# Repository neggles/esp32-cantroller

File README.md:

# EltekController

This is a little board I whipped up to connect to my [Eltek Flatpack2 Breakout Board](https://github.com/neg2led/EltekFlatpack2) but it should be useful as a general CANBUS control board with wide voltage input.

Most of the parts on the board are outfitted with their LCSC code for KiKit's JLCPCB SMT fab autogeneration. 

I'm using an ESP32-S2-WROOM / ESP32-S2-WROVER module, abusing the on-board USB DFU to avoid having a USB-UART IC.

There's a header designed to take a cheap AliExpress 1.3" 128x64 OLED module, a Qwiic connector for... reasons? and a footprint that matches ESP-Prog pinout and works with:

- Any 2x3 1.27mm IDC header, shrouded or unshrouded, or appropriate pogopin matrix
- Tag-Connect TC2030-NL programming pogopin connector
- Harwin Gecko 1.25mm pitch wire-to-board connector

There's probably some other stuff that'll fit just fine as well.

The DC-DC converter module is a fancy TDK-Lambda one which I got a whole bunch of from Digikey's Chip Outpost for like 20c each, when I run out I'll probably make another version using either an on-board converter or another module, one that outputs 5V so the Qwiic connector is actually in-spec and the XC6220 isn't solely used for USB-bus-powered mode.

To be honest, expect to see the on-board DC-DC version soon, because this module is C H O N K Y.

I've probably made some really bad design choices here, please don't judge me.

## Repository Structure
- `EltekController` contains the main schematics and board drawing
- `EltekController/EltekController.pretty` contains the board-specific footprints
- `EltekController/shapes3D` contains the 3D models for parts on the board (and a bunch of extras from my various experiments)

## Building
Simply call `make` in the top-top level directory. The `build` directory will then contain:

- the main board
- A panelized version of said board
- zipped gerbers for the boards you can directly use for manufacturing
- zipped gerbers and SMT assembly BOM/position files for JLCPCB's SMT assembly service for the single-board version.

Makefile uses [Jan Mrázek](https://github.com/yaqwsx)'s [KiKit](https://github.com/yaqwsx/KiKit), which I cannot recommend enough, and therefore has to be available on your system.

Jan's [jlcparts](https://yaqwsx.github.io/jlcparts/) app was also extremely useful in narrowing down part choices based on what JLCPCB have available.

-----
### **IMPORTANT NOTE:** If you give JLCPCB these files as-is, *please* verify the orientation of every part before submitting.

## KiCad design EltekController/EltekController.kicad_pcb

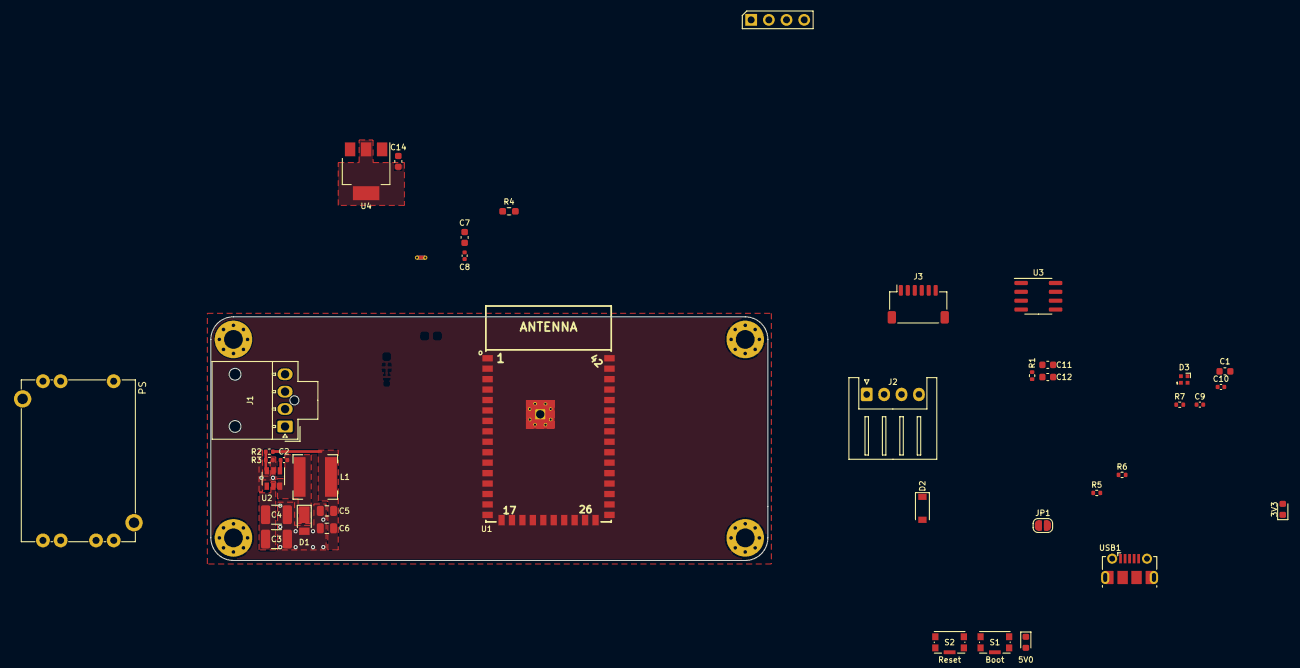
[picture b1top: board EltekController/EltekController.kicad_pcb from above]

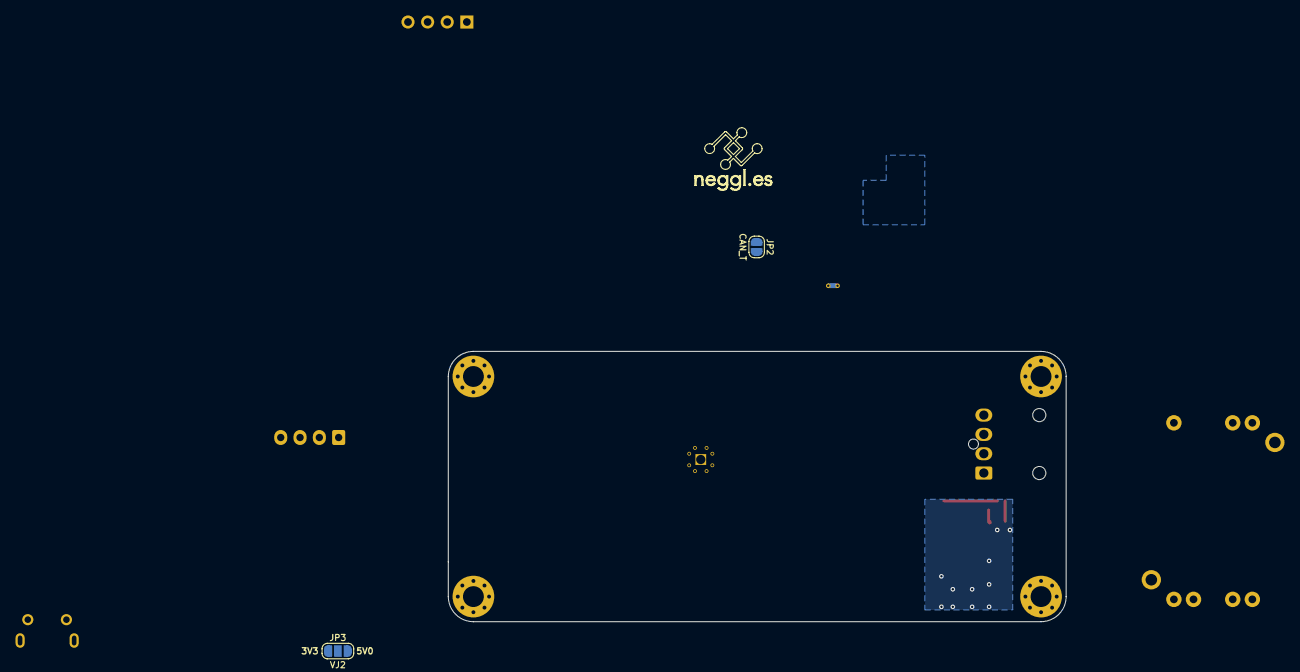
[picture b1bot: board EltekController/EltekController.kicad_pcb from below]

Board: 2 copper layers, 80.0 x 35.0 mm, 47 parts (3 on the bottom side), 31 nets.

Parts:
C1, C7: 10uF; C_0603_1608Metric
C2, C8, C9, C10: 100nF; C_0402_1005Metric
C3, C4: 2.2uF; C_1210_3225Metric_Pad1.33x2.70mm_HandSolder
C5, C6: 22uF; C_0805_2012Metric
C11, C14: 22uF; C_0603_1608Metric
C12: 100nF; C_0603_1608Metric
D1: SS210; D_PowerDI-123
D2: B5819W; D_SOD-123
D3: RGB; DY-S1515065_RGBC_6805-5T
D4: 3V3; LED_0603_1608Metric_SnapModel
D5: 5V0; LED_0603_1608Metric_SnapModel
H1, H2, H3, H4: MP; MountingHole_2.7mm_M2.5_Pad_Via
I2C1: OLED; OLED_SSD1315_128x64_1.3_I2C_New_Silhouette
J1: CANBUS; Molex_Nano-Fit_105309-xx04_1x04_P2.50mm_Vertical_Horizontal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
J2: Display; JST_XH_S4B-XH-A_1x04_P2.50mm_Horizontal
J3: ESP_PROG; JST_SH_SM06B-SRSS-TB_1x06-1MP_P1.00mm_Horizontal_3D
JP1: VPP_EN; SolderJumper-2_P1.3mm_Open_RoundedPad1.0x1.5mm
JP2: CAN_T; SolderJumper-2_P1.3mm_Open_RoundedPad1.0x1.5mm
JP3: VJ2; SolderJumper-3_P1.3mm_Open_RoundedPad1.0x1.5mm_NumberLabels
L1: 33uH; L_Sunlord_SWPA6028S
LOGO1: Logo_Open_Hardware_Small; neggle-logo-0.12
NT1: GND_TIE; NetTie-2_THT_Pad0.3mm
PS: Converter_DCDC_TDK-Lambda_CC3-xxxxxF-E
R1: 10K; R_0402_1005Metric
R2: 68K; R_0402_1005Metric
R3: 12K; R_0402_1005Metric
R4: 120R; R_0603_1608Metric_Pad0.98x0.95mm_HandSolder
R5: 22R; R_0402_1005Metric
R6, R7: 1K; R_0402_1005Metric
S1: Boot; SW_Push_1P1T-SH_NO_CK_KMR2xxG_3D
S2: Reset; SW_Push_1P1T-SH_NO_CK_KMR2xxG_3D
U1: ESP32-S2-WROVER; ESP32-S2-WROVER_and_WROOM(PCB,-I(IPEX))-Universal
U2: LMR16006XDDCR; SOT-23-6
U3: MAX3051ESA; SOIC-8_3.9x4.9mm_P1.27mm
U4: AMS1117-3.3; SOT-223-3_TabPin2
USB1: USB-OTG; USB_Micro-B_Molex-105017-0001

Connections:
+3V3: C7.2, C8.1, C11.2, C12.2, C14.2, D4.2, I2C1.2, JP1.1, JP3.3, R1.2, U1.2, U3.3, U4.2
+5V: C5.2, C6.2, D2.1, D3.2, D5.2, JP3.1, L1.2, R2.2, U4.3
+48V: C3.1, C4.1, J1.1, U2.5
/CAN+: J1.2, JP2.2, U3.7
/CAN-: J1.3, R4.1, U3.6
/CAN_RX: U1.16, U3.4
/CAN_TX: U1.15, U3.1
/CB: C2.2, U2.1
/D_RXSDA: J2.4, U1.32
/D_TXSCL: J2.3, U1.31
/FB: R2.1, R3.2, U2.3
/LED_DAT: R5.1, U1.30
/OLED_SCL: I2C1.3, U1.10
/OLED_SDA: I2C1.4, U1.9
/SW: C2.1, D1.1, L1.1, U2.6
/UART_RX: J3.3, U1.38
/UART_TX: J3.1, U1.37
/USB_D+: U1.23, USB1.3
/USB_D-: U1.22, USB1.2
/VBUS: D2.2, USB1.1
/VCC_PROG: J3.5, JP1.2
/~BOOT: C9.2, J3.2, S1.2, U1.3
/~CAN_EN: U1.14, U3.5
/~RST: C1.1, C10.2, J3.6, R1.1, S2.2, U1.41
GND: C1.2, C3.2, C4.2, C5.1, C6.1, C7.1, C8.2, C9.1, C10.1, C11.1, C12.1, C14.1, D1.2, D3.4, H2.1, H3.1, H4.1, I2C1.1, J2.1, J3.4, J3.MP, NT1.2, R3.1, R6.1, R7.1, S1.1, S2.1, U1.1, U1.26, U1.42, U1.43, U2.2, U3.2, U3.8, U4.1, USB1.5, USB1.6
GNDPWR: H1.1, J1.4, NT1.1
unnamed: D3.1, R5.2
unnamed: D4.1, R6.2
unnamed: D5.1, R7.2
unnamed: J2.2, JP3.2
unnamed: JP2.1, R4.2

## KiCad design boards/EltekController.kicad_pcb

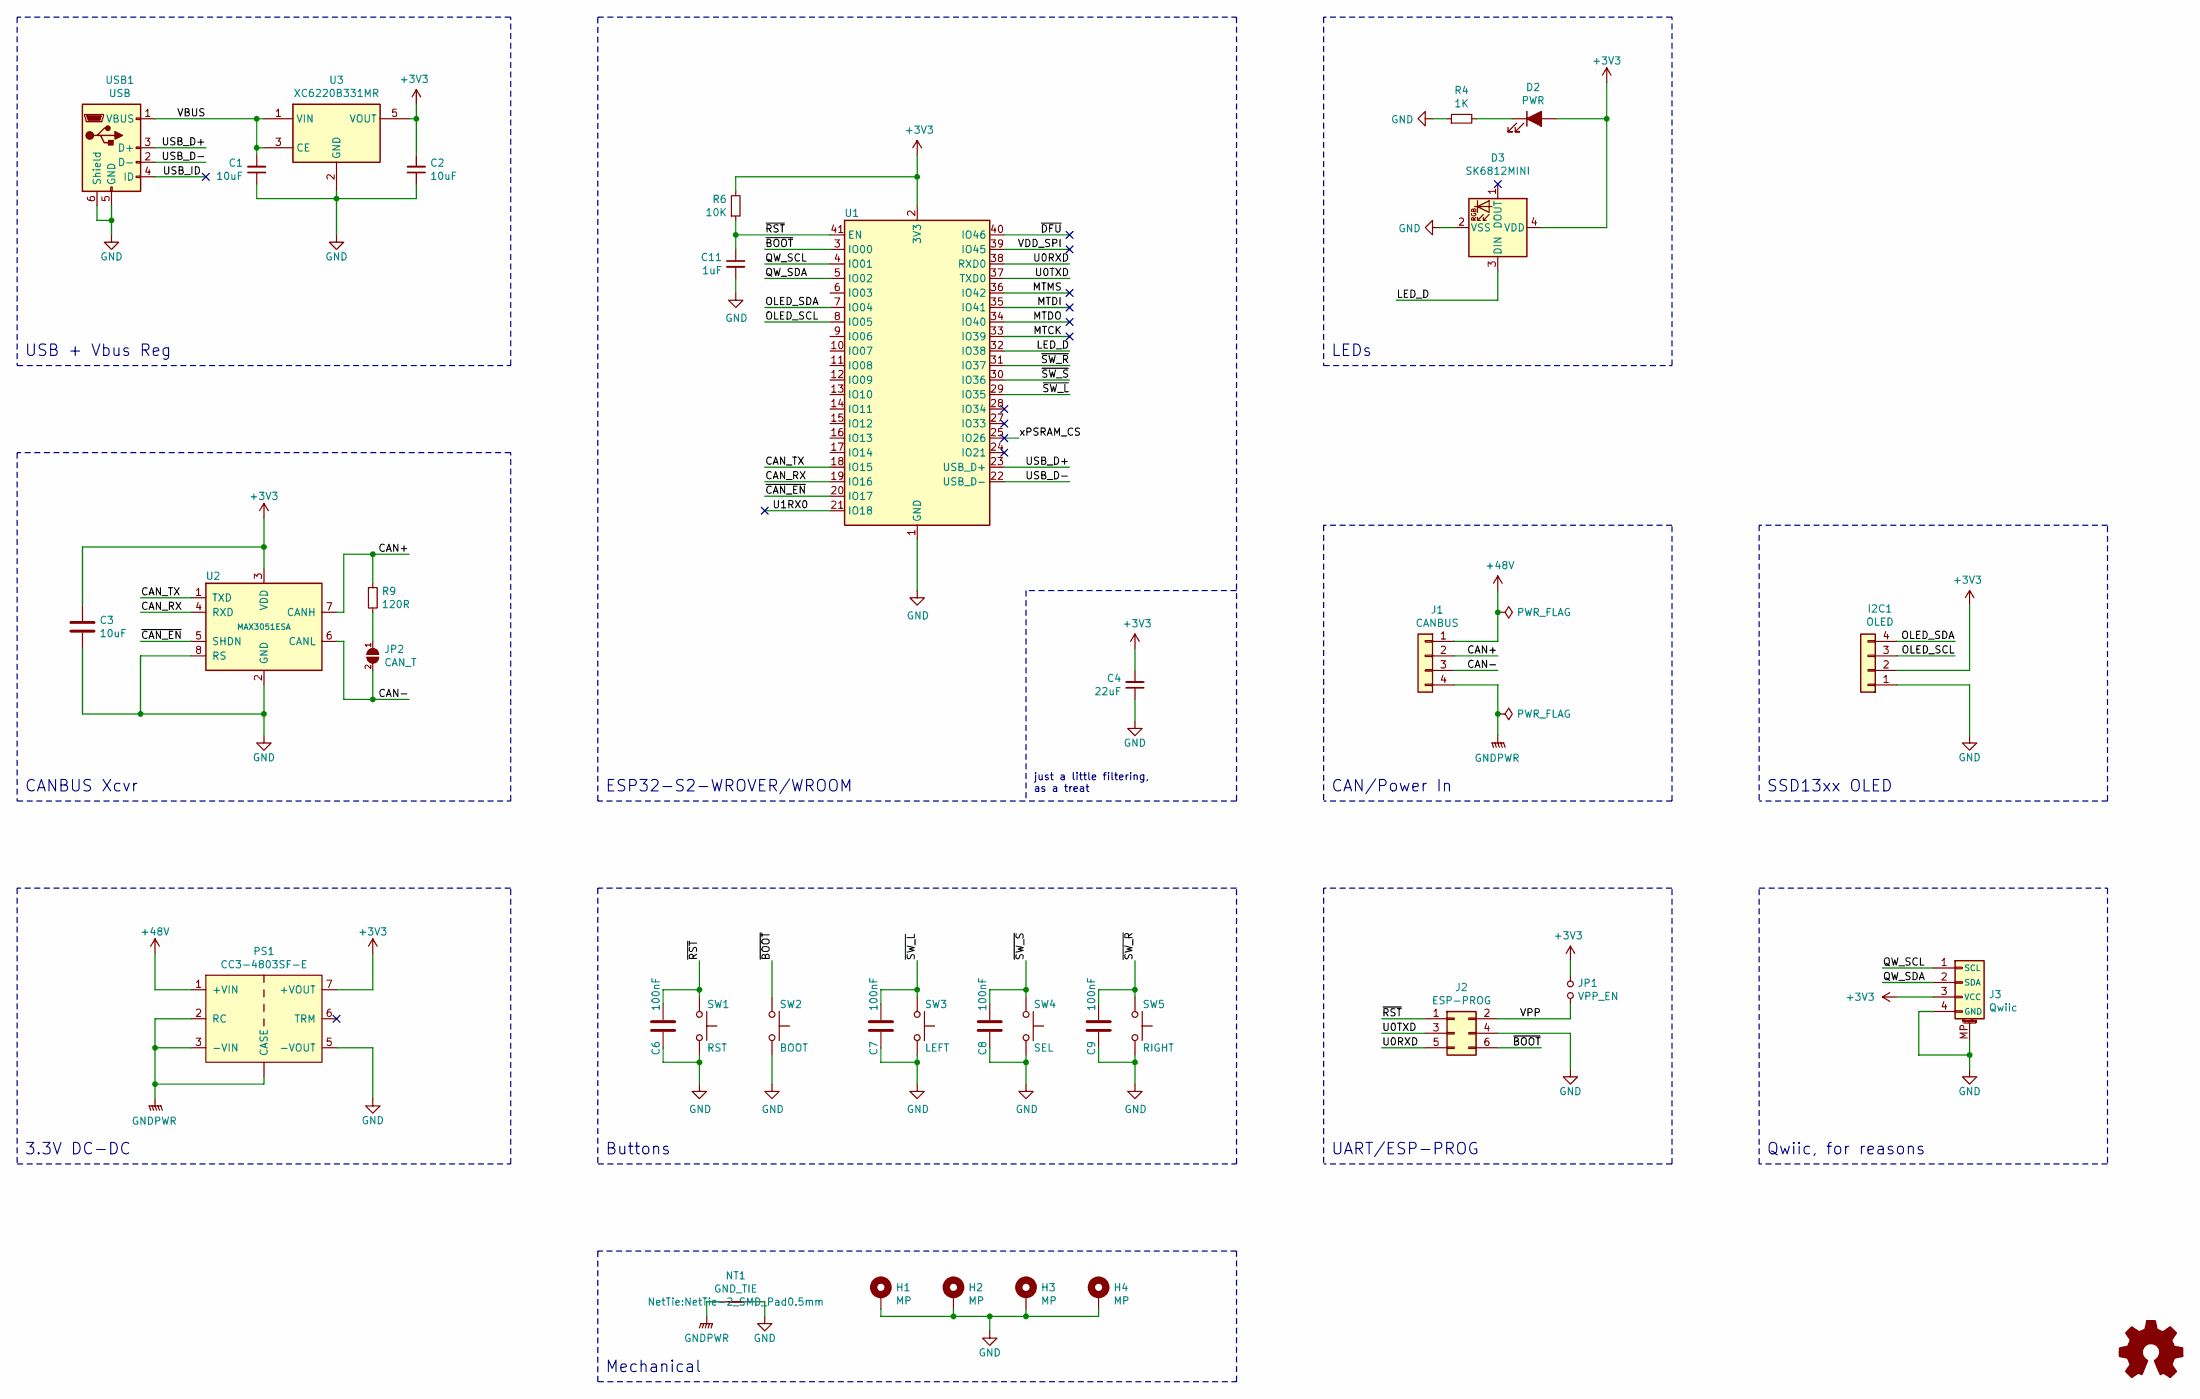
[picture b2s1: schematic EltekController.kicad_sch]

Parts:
C1, C2, C3: 10uF; C_0402_1005Metric; MPN CL05A106MQ5NUNC; LCSC C15525
C4: 22uF; C_0603_1608Metric; MPN CL10A226MQ8NRNC; LCSC C59461
C6, C7, C8, C9: 100nF; C_0402_1005Metric; MPN CL05B104KO5NNNC; LCSC C1525
C11: 1uF; C_0402_1005Metric; MPN CL05A105KA5NQNC; LCSC C52923
D2: PWR; LED_0603_1608Metric_SnapModel; MPN 19-217/GHC-YR1S2/3T; LCSC C72043
D3: SK6812MINI; LED_SK6812MINI_PLCC4_3.5x3.5mm_P1.75mm_3D
H1, H2, H3, H4: MP; MountingHole_2.7mm_M2.5_ISO7380_Pad_TopBottom
I2C1: OLED; OLED_SSD1315_128x64_1.3_I2C_New_Silhouette_Big3D
J1: CANBUS; Molex_Nano-Fit_105313-xx04_1x04_P2.50mm_Horizontal_3D
J2: ESP-PROG; Gecko-G125_PlusTC2030_IDCBox_2x03_P1.25mm_Vertical_3D
J3: Qwiic; JST_SH_SM04B-SRSS-TB_1x04-1MP_P1.00mm_Horizontal_3D
JP1: VPP_EN; SolderJumper-2_P1.3mm_Open_RoundedPad1.0x1.5mm
JP2: CAN_T; SolderJumper-2_P1.3mm_Open_RoundedPad1.0x1.5mm
LOGO1: Logo_Open_Hardware_Small; neggle-logo-0.12
NT1: GND_TIE; NetTie-2_SMD_Pad0.5mm
PS1: CC3-4803SF-E; Converter_DCDC_TDK-Lambda_CC3-xxxxxF-E
R4: 1K; R_0402_1005Metric; MPN 0402WGF1001TCE; LCSC C11702
R6: 10K; R_0402_1005Metric; MPN 0402WGF1002TCE; LCSC C25744
R9: 120R; R_0805_2012Metric_Pad1.15x1.40mm_HandSolder; MPN 0805W8F1200T5E; LCSC C17437
SW1: RST; KEY-SMD_4P-L4.2-W3.2-P2.20-LS5.1-TL; MPN K2-1808SN-A4SW-01; LCSC C92589
SW2: BOOT; KEY-SMD_4P-L4.2-W3.2-P2.20-LS5.1-TL; MPN K2-1808SN-A4SW-01; LCSC C92589
SW3: LEFT; KEY-SMD_4P-L4.2-W3.2-P2.20-LS5.1-TL; MPN K2-1808SN-A4SW-01; LCSC C92589
SW4: SEL; KEY-SMD_4P-L4.2-W3.2-P2.20-LS5.1-TL; MPN K2-1808SN-A4SW-01; LCSC C92589
SW5: RIGHT; KEY-SMD_4P-L4.2-W3.2-P2.20-LS5.1-TL; MPN K2-1808SN-A4SW-01; LCSC C92589
U1: ESP32-S2-WROVER; ESP32-S2-WROVER_and_WROOM(PCB,-I(IPEX))-Universal; MPN ESP32-S2-WROVER(4MB); LCSC C701333
U2: MAX3051ESA; SOIC-8_3.9x4.9mm_P1.27mm; MPN MAX3051ESA+T; LCSC C15648
U3: XC6220B331MR; SOT-23-5; LCSC C86534
USB1: USB; MICRO-USB-SMD_U254-051T-4BH83-F1S_C397452; LCSC C397452

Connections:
Board_1-+3V3: C2.2, C3.2, C4.2, D2.2 (A), D3.4 (VDD), I2C1.2, J3.3 (VCC), JP1.1, PS1.7 (+VOUT), R6.2, U1.2 (3V3), U2.3 (VDD), U3.5 (VOUT)
Board_1-+48V: J1.1, PS1.1 (+VIN)
Board_1-/CAN+: J1.2, R9.1, U2.7 (CANH)
Board_1-/CAN-: J1.3, JP2.2 (B), U2.6 (CANL)
Board_1-/CAN_RX: U1.19 (IO16), U2.4 (RXD)
Board_1-/CAN_TX: U1.18 (IO15), U2.1 (TXD)
Board_1-/LED_D: D3.3 (DIN), U1.32 (IO38)
Board_1-/MTCK: U1.33 (IO39)
Board_1-/MTDI: U1.35 (IO41)
Board_1-/MTDO: U1.34 (IO40)
Board_1-/MTMS: U1.36 (IO42)
Board_1-/OLED_SCL: I2C1.3, U1.8 (IO05)
Board_1-/OLED_SDA: I2C1.4, U1.7 (IO04)
Board_1-/QW_SCL: J3.1 (SCL), U1.4 (IO01)
Board_1-/QW_SDA: J3.2 (SDA), U1.5 (IO02)
Board_1-/U0RXD: J2.5, U1.38 (RXD0)
Board_1-/U0TXD: J2.3, U1.37 (TXD0)
Board_1-/U1RX0: U1.21 (IO18)
Board_1-/USB_D+: U1.23 (USB_D+), USB1.3 (D+)
Board_1-/USB_D-: U1.22 (USB_D-), USB1.2 (D-)
Board_1-/USB_ID: USB1.4 (ID)
Board_1-/VBUS: C1.2, U3.1 (VIN), U3.3 (CE), USB1.1 (VBUS)
Board_1-/VDD_SPI: U1.39 (IO45)
Board_1-/VPP: J2.2, JP1.2
Board_1-/xPSRAM_CS: U1.25 (IO26)
Board_1-/~CAN_EN: U1.20 (IO17), U2.5 (SHDN)
Board_1-/~DFU: U1.40 (IO46)
Board_1-/~SW_L: C7.2, SW3.1, U1.29 (IO35)
Board_1-/~SW_R: C9.2, SW5.1, U1.31 (IO37)
Board_1-/~SW_S: C8.2, SW4.1, U1.30 (IO36)
Board_1-GND: C1.1, C2.1, C3.1, C4.1, C6.1, C7.1, C8.1, C9.1, C11.2, D3.2 (VSS), H1.1, H2.1, H3.1, H4.1, I2C1.1, J2.4, J3.4 (GND), J3.MP (MountPin), NT1.2, PS1.5 (-VOUT), PS1.MP2, R4.1, SW1.2, SW2.2, SW3.2, SW4.2, SW5.2, U1.1 (GND), U1.26 (GND), U1.42 (GND), U1.43 (GND), U2.2 (GND), U2.8 (RS), U3.2 (GND), USB1.5 (GND), USB1.6 (Shield)
Board_1-GNDPWR: J1.4, NT1.1, PS1.2 (RC), PS1.3 (-VIN), PS1.MP (CASE)
Board_1-Net-(D2-Pad1): D2.1 (K), R4.2
Board_1-Net-(D3-Pad1): D3.1 (DOUT)
Board_1-Net-(JP2-Pad1): JP2.1 (A), R9.2
Board_1-Net-(PS1-Pad4): PS1.4 (NC)
Board_1-Net-(PS1-Pad6): PS1.6 (TRM)
Board_1-Net-(U1-Pad6): U1.6 (IO03)
Board_1-Net-(U1-Pad9): U1.9 (IO06)
Board_1-Net-(U1-Pad10): U1.10 (IO07)
Board_1-Net-(U1-Pad11): U1.11 (IO08)
Board_1-Net-(U1-Pad12): U1.12 (IO09)
Board_1-Net-(U1-Pad13): U1.13 (IO10)
Board_1-Net-(U1-Pad14): U1.14 (IO11)
Board_1-Net-(U1-Pad15): U1.15 (IO12)
Board_1-Net-(U1-Pad16): U1.16 (IO13)
Board_1-Net-(U1-Pad17): U1.17 (IO14)
Board_1-Net-(U1-Pad24): U1.24 (IO21)
Board_1-Net-(U1-Pad27): U1.27 (IO33)
Board_1-Net-(U1-Pad28): U1.28 (IO34)
Board_1-Net-(U3-Pad4): U3.4 (NC)

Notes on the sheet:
Qwiic, for reasons
UART/ESP-PROG
CAN/Power In
3.3V DC-DC
Buttons
SSD13xx OLED
ESP32-S2-WROVER/WROOM
Mechanical
just a little filtering, as a treat
CANBUS Xcvr
LEDs
USB + Vbus Reg

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
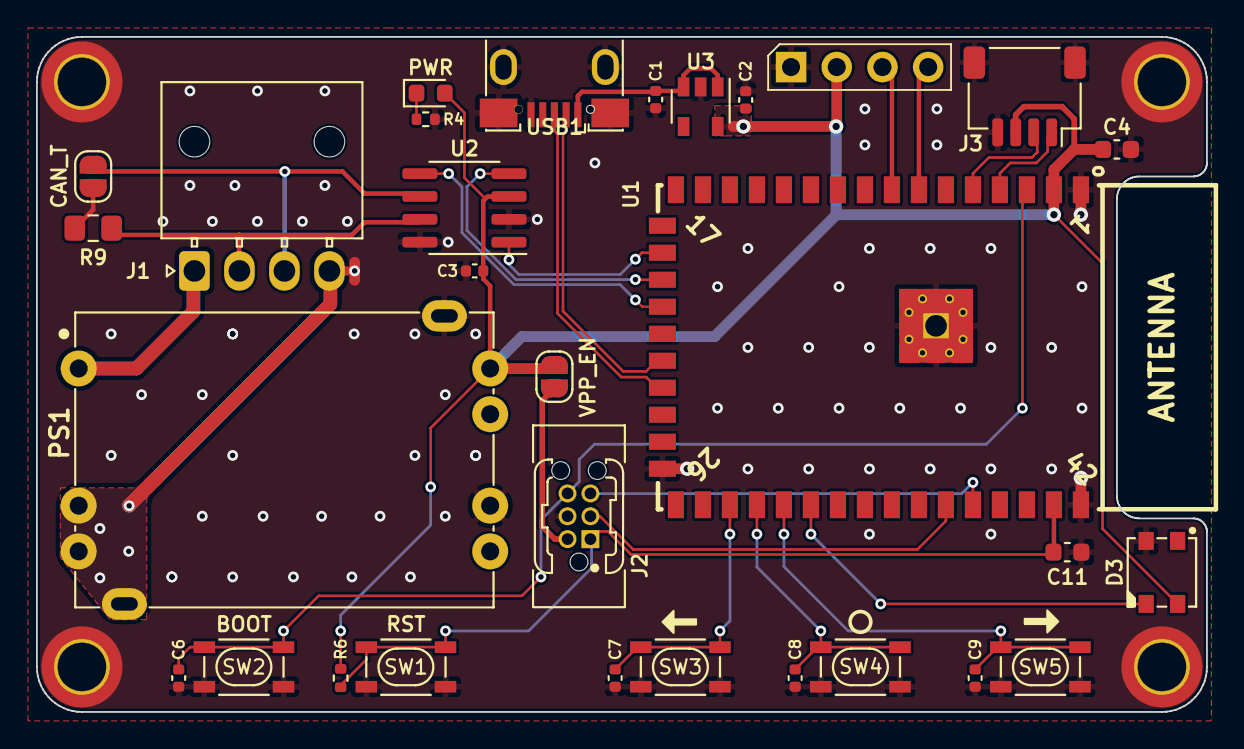
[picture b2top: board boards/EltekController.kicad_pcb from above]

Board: 2 copper layers, 65.0 x 37.5 mm, 36 parts (1 on the bottom side), 27 nets.

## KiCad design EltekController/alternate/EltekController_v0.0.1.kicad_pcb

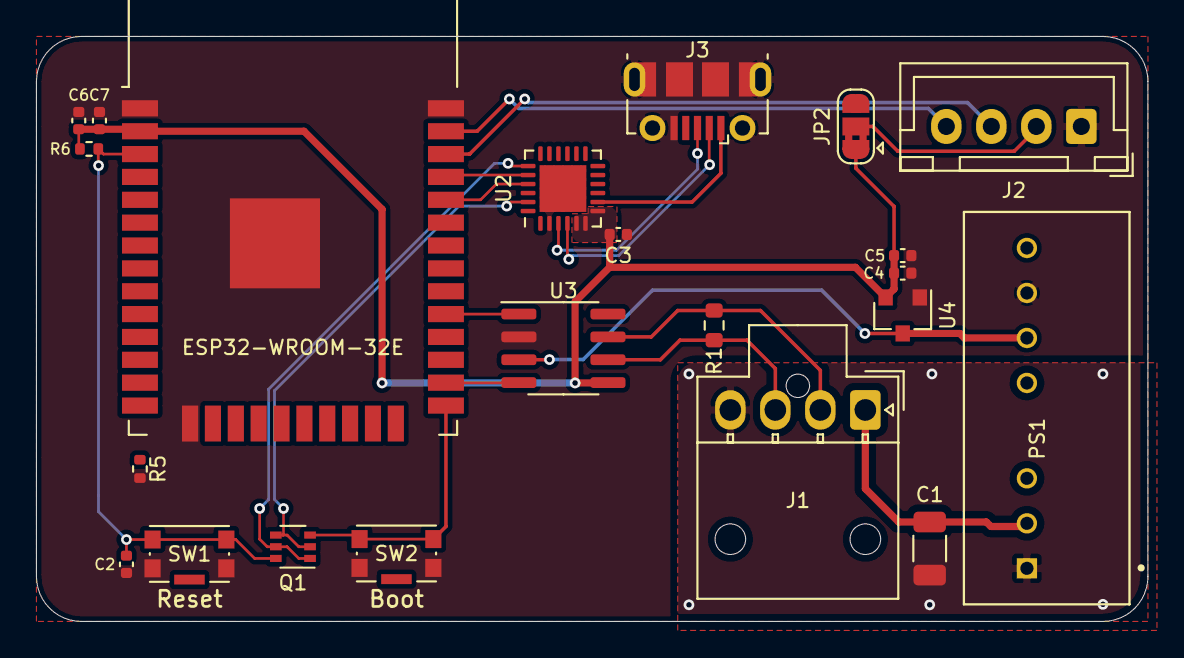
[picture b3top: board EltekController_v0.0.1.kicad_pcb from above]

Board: 4 copper layers, 61.8 x 32.5 mm, 22 parts (0 on the bottom side), 22 nets.

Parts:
C1: 1uF; C_1206_3216Metric
C2, C5, C7: 1uF; C_0402_1005Metric
C3, C4, C6: 10uF; C_0402_1005Metric
J1: PSU CAN; Molex_Nano-Fit_105309-xx04_1x04_P2.50mm_Vertical_Horizontal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
J2: Display; JST_XH_B4B-XH-A_1x04_P2.50mm_Vertical
J3: USB_B_Micro; USB_Micro-B_Molex-105017-0001
JP2: VDISP_SEL; SolderJumper-3_P1.3mm_Bridged2Bar12_RoundedPad1.0x1.5mm
PS1: SPBW06G-05; CONV_SPBW06F-12
Q1: UMH3N; SOT-363_SC-70-6
R1: 120R; R_0603_1608Metric
R5, R6: 10K; R_0402_1005Metric
SW1: Reset; SW_Push_1P1T-SH_NO_CK_KMR2xxG_3D
SW2: Boot; SW_Push_1P1T-SH_NO_CK_KMR2xxG_3D
U1: ESP32-WROOM-32E; ESP32-WROOM-32
U2: CP2104-F03-GMR; QFN-24-1EP_4x4mm_P0.5mm_EP2.6x2.6mm
U3: TJA1051T/3/1J; SOIC-8_3.9x4.9mm_P1.27mm
U4: XC6206P332MR; SOT-23

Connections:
+3V3: C3.2, C4.2, C5.2, C6.2, C7.2, JP2.1, R6.2, U1.2, U2.5, U2.6, U2.7, U3.5, U4.2
+5V: JP2.3, PS1.6, U3.3, U4.3
+48V: C1.2, J1.1, PS1.2
/CAN+: J1.2, R1.2, U3.7
/CAN-: J1.3, R1.1, U3.6
/CAN_RX: U1.26, U3.4
/CAN_TX: U1.29, U3.1
/DTR: Q1.2, Q1.4, U2.23
/RTS: Q1.1, Q1.5, U2.19
/SCL_TX: J2.3, U1.36
/SDA_RX: J2.4, U1.37
/UART_RX: U1.34, U2.21
/UART_TX: U1.35, U2.20
/USB_D+: J3.3, U2.3
/USB_D-: J3.2, U2.4
/VBUS: J3.1, U2.8
/~BOOT: Q1.3, SW2.2, U1.25
/~GPIO12: R5.2, U1.14
/~RST: C2.1, Q1.6, R6.1, SW1.2, U1.3
GND: C2.2, C3.1, C4.1, C5.1, C6.1, C7.1, J2.1, J3.5, J3.6, PS1.7, R5.1, SW1.1, SW2.1, U1.1, U1.15, U1.38, U1.39, U2.2, U2.25, U3.2, U4.1
GNDPWR: C1.1, J1.4, PS1.1
unnamed: J2.2, JP2.2

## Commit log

2021-02-08 initial commit, probably missing some STEPs etc
2021-02-08 oops don't need those files no sir
2021-02-08 fixup readme.md, hope travis works this time
2021-02-08 fix makefile
2021-02-08 fixup readme.md
2021-02-08 updoots
2021-02-10 move nextion hmi file
2021-02-12 update it so the thing kinda works
2021-02-13 v0.1
2021-02-13 tweak panel size
2021-02-19 Squashed commit of the following:
    commit 90807526c89bbe23d0d14403179393f46968545b
    Author: neg2led <4232981+neg2led@users.noreply.github.com>
    Date: Fri Feb 19 13:40:56 2021 +1100
    change vtabs
    commit bdeb0cb4df280460f20d9cb7594185681e97bdea
    Author: neg2led <4232981+neg2led@users.noreply.github.com>
2021-02-19 fixup ESP32 placement pos
2021-02-21 update, drop firmware folder out for now
2021-02-25 saving this because I changed my mind again
2021-03-07 yes, good
2021-03-08 updoot, new rev
2021-03-08 update doco a bit
2021-03-08 add 3d models and internalize footprints
2021-03-08 oops. update makefile for new board size
2021-03-08 switch to nano-fit, but any 2.54 or 2.5mm header works
2021-03-08 missed a trace
2021-03-08 micro-usb footprint fixup
2021-03-18 flip VCC and GND on the OLED... sigh
2021-04-06 Revert "flip VCC and GND on the OLED... sigh"
    This reverts commit 16d08c3f3e759163bdd9650e3550ba9f731368f2.
2021-04-06 Deploy neg2led/esp32-cantroller to github.com/neg2led/esp32-cantroller.git:gh-pages
2021-04-15 Deploying to gh-pages from @ neg2led/esp32-cantroller@cb1a9baeedd98c80de610074800ab9d85ac567da 🚀
2021-04-18 Deploying to gh-pages from @ neg2led/esp32-cantroller@76902b338b0b501c95a8f4f6464eea3f3eddbee0 🚀
2021-04-18 fix action
2021-04-18 updoot
2021-04-18 license update
2021-04-18 Deploying to gh-pages from @ neg2led/esp32-cantroller@9e89654d6dfeae13c7be468706d1b1205d629a69 🚀
2021-04-18 Deploying to gh-pages from @ neg2led/esp32-cantroller@bba46f7c44b3983ce4b2cce59a1c126a2482bb3f 🚀
2022-11-22 add .gitattributes
